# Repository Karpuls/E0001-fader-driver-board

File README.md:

# E0001 – Motorized fader driver board

Controller board for an ALPS **RSA0N11M9A0J**-compatible motorized, touch-sensitive 100 mm fader
(Amazon.de B0H45B29YK clone). The board mounts under the fader, soldered to its pins.

- **Rev B (current):** STM32C051F6P6, DRV8210P H-bridge (motor from 5 V), MCP1703A 3.3 V LDO,
  capacitive touch on the fader lever, position from the 10k linear track, 4-layer, 107 × 17 mm.
- **Interface:** JST GH 4-pin horizontal, Pixhawk/Dronecode I2C pinout (1 = +5 V, 2 = SCL, 3 = SDA, 4 = GND).
  I2C pull-ups belong on the host. Address via 3 solder jumpers (bottom side), SWD via Tag-Connect TC2030-NL pads (bottom).
- Rev A (2-layer, STM32G031) is kept in `archive/revA/`.

## Layout
| Path | Content |
|---|---|
| `E0001_fader_driver.kicad_pro/.kicad_sch/.kicad_pcb` | KiCad 10 project |
| `lib/` | Fader symbol/footprint/3D model + notes, STM32C051F6Px symbol |
| `bom/E0001_revB_digikey_bom.csv` | BOM (DigiKey LV part numbers, excl. fader and JST connector) |
| `mech/` | Board + fader assembly STEP and renders |
| `build/scripts/` | Generators: schematic, placement, pre-routes, Freerouting pipeline, refs, BOM (`run_all.sh`) |

## Open points
Verify the clone fader's hole pattern and pin orientation on a sample before ordering PCBs (see `lib/ALPS_RSA0N11M9A0J_notes.md`).
The ALPS 3D model in `lib/3dmodels` is ALPS CAD data; check ALPS terms before making this repository public.

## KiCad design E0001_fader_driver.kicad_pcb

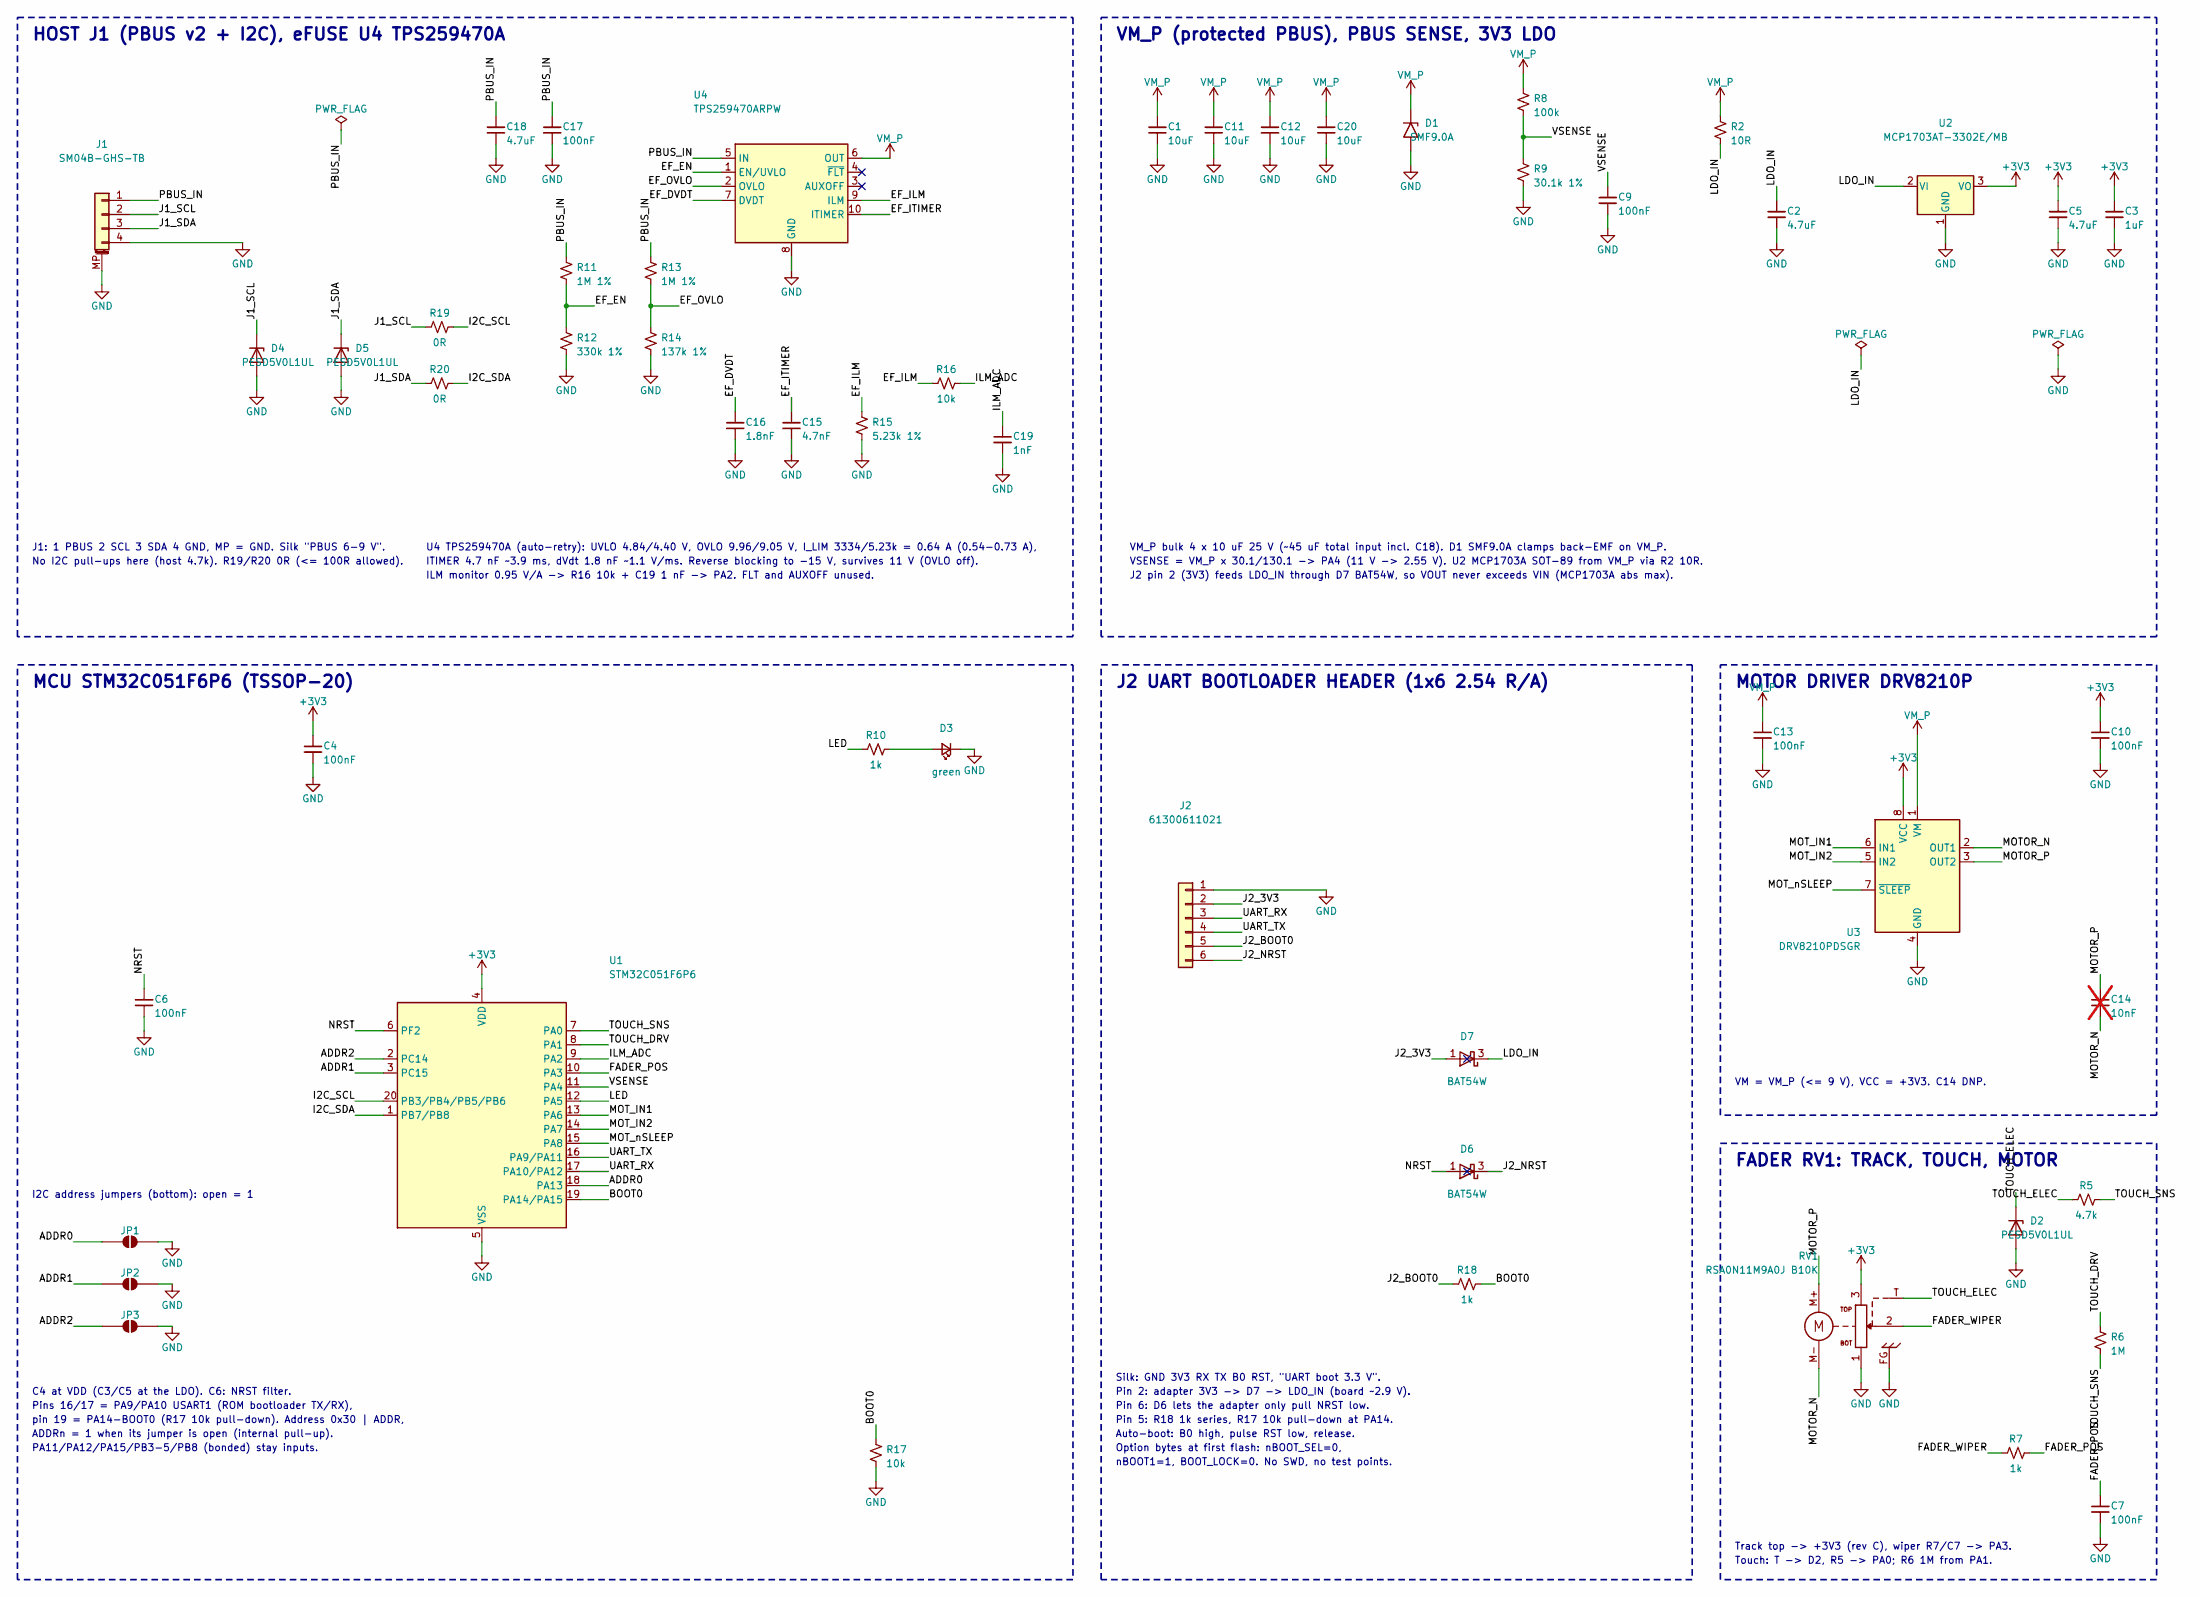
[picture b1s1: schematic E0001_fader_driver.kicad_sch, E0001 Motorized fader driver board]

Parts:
C1, C11, C12, C20: 10uF; C_0805_2012Metric; Voltage 25V; MPN TMK212BBJ106MG-T
C2, C5, C18: 4.7uF; C_0603_1608Metric; Voltage 25V; MPN GRM188R61E475KE11D
C3: 1uF; C_0402_1005Metric; MPN CL05A105KP5NNNC
C4, C6, C7, C9, C10, C13, C17: 100nF; C_0402_1005Metric; Voltage 50V; MPN GRM155R71H104KE14D
C14: 10nF; C_0402_1005Metric; Voltage 50V; MPN GRM155R71H103KA88D; not fitted
C15: 4.7nF; C_0402_1005Metric; Voltage 50V; MPN GRM155R71H472KA01J
C16: 1.8nF; C_0402_1005Metric; Voltage 50V; MPN C0402C182K5RACTU
C19: 1nF; C_0402_1005Metric; Voltage 50V; MPN GRM155R71H102KA01D
D1: SMF9.0A; D_SOD-123F; MPN SMF9.0A
D2, D4, D5: PESD5V0L1UL; D_SOD-882; MPN PESD5V0L1UL,315
D3: green; LED_0603_1608Metric; MPN LTST-C191KGKT
D6, D7: BAT54W; SOT-323_SC-70; MPN BAT54W,135
J1: SM04B-GHS-TB; JST_GH_SM04B-GHS-TB_1x04-1MP_P1.25mm_Horizontal; MPN SM04B-GHS-TB(LF)(SN)
J2: 61300611021; PinHeader_1x06_P2.54mm_Horizontal; MPN 61300611021
JP1: ADDR0; SolderJumper-2_P1.3mm_Open_RoundedPad1.0x1.5mm
JP2: ADDR1; SolderJumper-2_P1.3mm_Open_RoundedPad1.0x1.5mm
JP3: ADDR2; SolderJumper-2_P1.3mm_Open_RoundedPad1.0x1.5mm
R2: 10R; R_0603_1608Metric; MPN RC0603FR-0710RL
R5: 4.7k; R_0402_1005Metric; MPN RK73H1ETTP4701F
R6: 1M; R_0402_1005Metric; MPN RC0402FR-071ML
R7, R10, R18: 1k; R_0402_1005Metric; MPN RC0402FR-071KL
R8: 100k; R_0402_1005Metric; MPN RC0402FR-07100KL
R9: 30.1k 1%; R_0402_1005Metric; MPN RC0402FR-0730K1L
R11, R13: 1M 1%; R_0402_1005Metric; MPN RC0402FR-071ML
R12: 330k 1%; R_0402_1005Metric; MPN RC0402FR-07330KL
R14: 137k 1%; R_0402_1005Metric; MPN RC0402FR-07137KL
R15: 5.23k 1%; R_0402_1005Metric; MPN RC0402FR-075K23L
R16, R17: 10k; R_0402_1005Metric; MPN RC0402FR-0710KL
R19, R20: 0R; R_0402_1005Metric; MPN RC0402JR-070RL
RV1: RSA0N11M9A0J B10K; ALPS_RSA0N11M9A0J; MPN RSA0N11M9A0J B10K clone
U1: STM32C051F6P6; TSSOP-20_4.4x6.5mm_P0.65mm; MPN STM32C051F6P6
U2: MCP1703AT-3302E/MB; SOT-89-3; MPN MCP1703AT-3302E/MB
U3: DRV8210PDSGR; Texas_DSG0008A_WSON-8-1EP_2x2mm_P0.5mm_EP0.9x1.6mm; MPN DRV8210PDSGR
U4: TPS259470ARPW; TI_RPW0010A_VQFN-HR-10_2x2mm_P0.475mm; MPN TPS259470ARPWR

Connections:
+3V3: C3.1, C4.1, C5.1, C10.1, RV1.3 (END_TOP), U1.4 (VDD), U2.3 (VO), U3.8 (VCC)
/ADDR0: JP1.1 (A), U1.18 (PA13)
/ADDR1: JP2.1 (A), U1.3 (PC15)
/ADDR2: JP3.1 (A), U1.2 (PC14)
/BOOT0: R17.1, R18.2, U1.19 (PA14/PA15)
/EF_DVDT: C16.1, U4.7 (DVDT)
/EF_EN: R11.2, R12.1, U4.1 (EN/UVLO)
/EF_ILM: R15.1, R16.1, U4.9 (ILM)
/EF_ITIMER: C15.1, U4.10 (ITIMER)
/EF_OVLO: R13.2, R14.1, U4.2 (OVLO)
/FADER_POS: C7.1, R7.2, U1.10 (PA3)
/FADER_WIPER: R7.1, RV1.2 (WIPER)
/I2C_SCL: R19.2, U1.20 (PB3/PB4/PB5/PB6)
/I2C_SDA: R20.2, U1.1 (PB7/PB8)
/ILM_ADC: C19.1, R16.2, U1.9 (PA2)
/J1_SCL: D4.1 (K), J1.2, R19.1
/J1_SDA: D5.1 (K), J1.3, R20.1
/J2_3V3: D7.1 (A), J2.2
/J2_BOOT0: J2.5, R18.1
/J2_NRST: D6.3 (K), J2.6
/LDO_IN: C2.1, D7.3 (K), R2.2, U2.2 (VI)
/LED: R10.1, U1.12 (PA5)
/MOTOR_N: C14.2, RV1.M-, U3.2 (OUT1)
/MOTOR_P: C14.1, RV1.M+, U3.3 (OUT2)
/MOT_IN1: U1.13 (PA6), U3.6 (IN1)
/MOT_IN2: U1.14 (PA7), U3.5 (IN2)
/MOT_nSLEEP: U1.15 (PA8), U3.7 (~SLEEP)
/NRST: C6.1, D6.1 (A), U1.6 (PF2)
/PBUS_IN: C17.1, C18.1, J1.1, R11.1, R13.1, U4.5 (IN)
/TOUCH_DRV: R6.1, U1.8 (PA1)
/TOUCH_ELEC: D2.1 (K), R5.1, RV1.T (TOUCH)
/TOUCH_SNS: R5.2, R6.2, U1.7 (PA0)
/UART_RX: J2.3, U1.17 (PA10/PA12)
/UART_TX: J2.4, U1.16 (PA9/PA11)
/VSENSE: C9.1, R8.2, R9.1, U1.11 (PA4)
GND: C1.2, C2.2, C3.2, C4.2, C5.2, C6.2, C7.2, C9.2, C10.2, C11.2, C12.2, C13.2, C15.2, C16.2, C17.2, C18.2, C19.2, C20.2, D1.2 (A2), D2.2 (A), D3.1 (K), D4.2 (A), D5.2 (A), J1.4, J1.MP (MountPin), J2.1, JP1.2 (B), JP2.2 (B), JP3.2 (B), R9.2, R12.2, R14.2, R15.2, R17.2, RV1.1 (END_BOT), RV1.FG (FRAME), U1.5 (VSS), U2.1 (GND), U3.4 (GND), U3.9 (GND), U4.8 (GND)
unnamed: D3.2 (A), R10.2
VM_P: C1.1, C11.1, C12.1, C13.1, C20.1, D1.1 (A1), R2.1, R8.1, U3.1 (VM), U4.6 (OUT)

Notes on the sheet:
HOST J1 (PBUS v2 + I2C), eFUSE U4 TPS259470A
J1: 1 PBUS 2 SCL 3 SDA 4 GND, MP = GND. Silk "PBUS 6-9 V".
No I2C pull-ups here (host 4.7k). R19/R20 0R (<= 100R allowed).
U4 TPS259470A (auto-retry): UVLO 4.84/4.40 V, OVLO 9.96/9.05 V, I_LIM 3334/5.23k = 0.64 A (0.54-0.73 A),
ITIMER 4.7 nF ~3.9 ms, dVdt 1.8 nF ~1.1 V/ms. Reverse blocking to -15 V, survives 11 V (OVLO off).
ILM monitor 0.95 V/A -> R16 10k + C19 1 nF -> PA2. FLT and AUXOFF unused.
VM_P (protected PBUS), PBUS SENSE, 3V3 LDO
VM_P bulk 4 x 10 uF 25 V (~45 uF total input incl. C18). D1 SMF9.0A clamps back-EMF on VM_P.
VSENSE = VM_P x 30.1/130.1 -> PA4 (11 V -> 2.55 V). U2 MCP1703A SOT-89 from VM_P via R2 10R.
J2 pin 2 (3V3) feeds LDO_IN through D7 BAT54W, so VOUT never exceeds VIN (MCP1703A abs max).
MCU STM32C051F6P6 (TSSOP-20)
C4 at VDD (C3/C5 at the LDO). C6: NRST filter.
Pins 16/17 = PA9/PA10 USART1 (ROM bootloader TX/RX),
pin 19 = PA14-BOOT0 (R17 10k pull-down). Address 0x30 | ADDR,
ADDRn = 1 when its jumper is open (internal pull-up).
PA11/PA12/PA15/PB3-5/PB8 (bonded) stay inputs.
I2C address jumpers (bottom): open = 1
J2 UART BOOTLOADER HEADER (1x6 2.54 R/A)
Silk: GND 3V3 RX TX B0 RST, "UART boot 3.3 V".
Pin 2: adapter 3V3 -> D7 -> LDO_IN (board ~2.9 V).
Pin 6: D6 lets the adapter only pull NRST low.
Pin 5: R18 1k series, R17 10k pull-down at PA14.
Auto-boot: B0 high, pulse RST low, release.
Option bytes at first flash: nBOOT_SEL=0,
nBOOT1=1, BOOT_LOCK=0. No SWD, no test points.
MOTOR DRIVER DRV8210P
VM = VM_P (<= 9 V), VCC = +3V3. C14 DNP.
FADER RV1: TRACK, TOUCH, MOTOR
Track top -> +3V3 (rev C), wiper R7/C7 -> PA3.
Touch: T -> D2, R5 -> PA0; R6 1M from PA1.

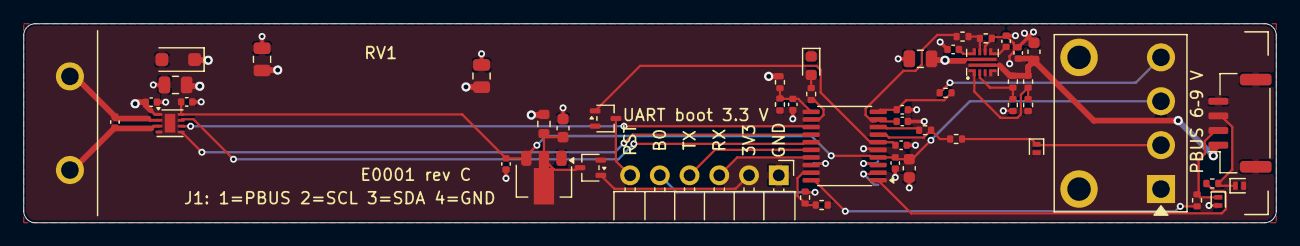
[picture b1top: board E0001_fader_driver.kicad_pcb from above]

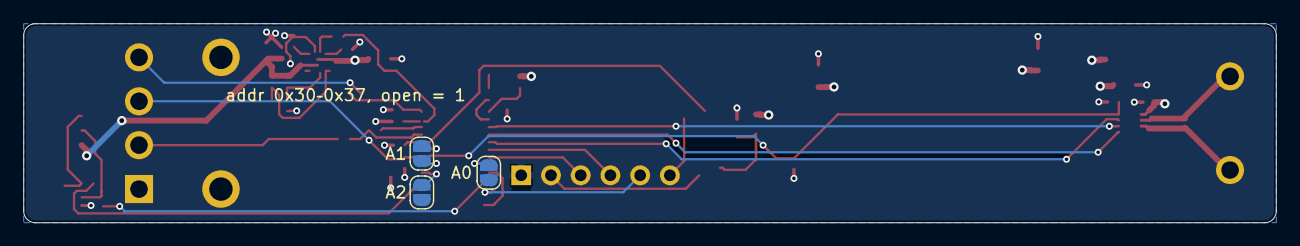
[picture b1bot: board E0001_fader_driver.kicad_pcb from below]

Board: 4 copper layers, 107.0 x 17.0 mm, 53 parts (3 on the bottom side), 38 nets.

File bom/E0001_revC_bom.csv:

Supplier,Qty,QtyBasis,References,Value,Footprint,MPN,Manufacturer,SupplierPN,Stock,Lifecycle,UnitEUR,LeadWeeks,DNP,OwnerStock,Notes
DigiKey,1,spec,U1,STM32C051F6P6,TSSOP-20,STM32C051F6P6,STMicroelectronics,497-STM32C051F6P6-ND,47,Active,1.28,52,,no,"Approved alternate STM32C051F8P6 (same TSSOP-20 pinout, 64 KB): 497-STM32C051F8P6-ND, stock 1178, EUR 1.34. Buy whichever is in stock."
DigiKey,1,spec,U2,3.3 V LDO,**SOT-89-3**,MCP1703AT-3302E/MB,Microchip Technology,MCP1703AT-3302E/MBCT-ND,9366,Active,0.66,8,,no,
DigiKey,1,spec,U3,H-bridge,WSON-8 2×2,DRV8210PDSGR,Texas Instruments,296-DRV8210PDSGRCT-ND,3849,Active,0.76,12,,no,
DigiKey,1,spec,U4,eFuse,VQFN-HR-10 2×2 (RPW),TPS259470ARPWR,Texas Instruments,296-TPS259470ARPWRCT-ND,78910,Active,1.81,12,,no,
LCSC,1,spec,J1,JST-GH 4p,SM04B-GHS-TB horizontal,SM04B-GHS-TB(LF)(SN),JST Sales America Inc.,LCSC C189895 (SM04B-GHS-TB(LF)(SN)),"1900 (LCSC, 2026-10-19)",Active,0.31 USD @5 (LCSC),16,,yes,"DigiKey 455-1566-1-ND stock 0 (16 w). Second sources: RS Online 1755704 / 7521797 (regional stock), LCSC C189895 (min order 5). E0003 uses the same LCSC part."
DigiKey,1,spec,J2,1×6 2.54 R/A,PinHeader_1x06_P2.54mm_Horizontal,61300611021,Würth Elektronik,732-5339-ND,6816,Active,0.47,18,,no,
Amazon.de,1,spec,RV1,Motor fader 10 k lin,ALPS_RSA0N11M9A0J,RSA0N11M9A0J B10K clone,Fastigeaty (seller Fadianshop),ASIN B0H45B29YK,not checked (Amazon page blocked),-,,,,yes,"ALPS RSA0N11M9A0J-compatible clone, 100 mm motor fader Owner has the faders (flag only; full quantity stays)."
DigiKey,1,spec,D1,SMF9.0A,D_SOD-123F (SMF),SMF9.0A,Littelfuse Inc.,F5755CT-ND,2437,Active,0.47,20,,no,
DigiKey,3,spec,D2 D4 D5,ESD,D_SOD-882,"PESD5V0L1UL,315",Nexperia USA Inc.,1727-4193-1-ND,18740,Active,0.22,30,,no,
DigiKey,1,spec,D3,LED green,0603,LTST-C191KGKT,Lite-On Inc.,160-1446-1-ND,2812317,Active,0.13,14,,no,
DigiKey,2,spec,D6 D7,Schottky,SOT-323,"BAT54W,135",Nexperia USA Inc.,1727-1869-1-ND,26776,Active,0.17,30,,no,
DigiKey,4,spec,C1 C11 C12 C20,10 µF 25 V X5R,0805,TMK212BBJ106MG-T,Taiyo Yuden,587-6025-1-ND,237658,Active,0.18,23,,no,
DigiKey,3,spec,C2 C5 C18,4.7 µF 25 V,0603,GRM188R61E475KE11D,Murata Electronics,490-7203-1-ND,713624,Active,0.21,17,,no,
DigiKey,1,spec,C3,1 µF 10 V,0402,CL05A105KP5NNNC,Samsung Electro-Mechanics,1276-1076-1-ND,911254,Active,0.09,61,,no,
DigiKey,7,spec,C4 C6 C7 C9 C10 C13 C17,100 nF 50 V X7R,0402,GRM155R71H104KE14D,Murata Electronics,490-10700-1-ND,1430736,Active,0.09,17,,no,
DigiKey,1,spec,C14,10 nF 50 V,0402,GRM155R71H103KA88D,Murata Electronics,490-4516-1-ND,4127456,Active,0.09,17,DNP,no,
DigiKey,1,spec,C15,4.7 nF 50 V (ITIMER),0402,GRM155R71H472KA01J,Murata Electronics,490-8259-1-ND,143253,Active,0.09,17,,no,
DigiKey,1,spec,C16,1.8 nF 50 V (dVdt),0402,C0402C182K5RACTU,KEMET,399-C0402C182K5RACTUCT-ND,9731,Active,0.44,17,,no,
DigiKey,1,spec,C19,1 nF 50 V (ILM ADC),0402,GRM155R71H102KA01D,Murata Electronics,490-1303-1-ND,4189153,Active,0.1,21,,no,
DigiKey,1,spec,R2,10 Ω,0603,RC0603FR-0710RL,YAGEO,311-10.0HRCT-ND,264276,Active,0.1,22,,no,
DigiKey,1,spec,R5,4.7 kΩ,0402,RK73H1ETTP4701F,"KOA Speer Electronics, Inc.",2019-RK73H1ETTP4701FCT-ND,2889565,Active,0.09,7,,no,
DigiKey,3,spec,R6 R11 R13,1 MΩ 1 %,0402,RC0402FR-071ML,YAGEO,311-1.00MLRCT-ND,961162,Active,0.09,22,,no,
DigiKey,3,spec,R7 R10 R18,1 kΩ,0402,RC0402FR-071KL,YAGEO,311-1.00KLRCT-ND,3584811,Active,0.09,22,,no,
DigiKey,1,spec,R8,100 kΩ,0402,RC0402FR-07100KL,YAGEO,311-100KLRCT-ND,6147223,Active,0.09,22,,no,
DigiKey,1,spec,R9,30.1 kΩ 1 %,0402,RC0402FR-0730K1L,YAGEO,311-30.1KLRCT-ND,12740,Active,0.09,22,,no,
DigiKey,1,spec,R12,330 kΩ 1 %,0402,RC0402FR-07330KL,YAGEO,311-330KLRCT-ND,902151,Active,0.09,22,,no,
DigiKey,1,spec,R14,137 kΩ 1 %,0402,RC0402FR-07137KL,YAGEO,YAG2972CT-ND,126860,Active,0.09,22,,no,
DigiKey,1,spec,R15,5.23 kΩ 1 %,0402,RC0402FR-075K23L,YAGEO,YAG3195CT-ND,39950,Active,0.09,22,,no,
DigiKey,2,spec,R16 R17,10 kΩ,0402,RC0402FR-0710KL,YAGEO,311-10.0KLRCT-ND,10874291,Active,0.09,22,,no,
DigiKey,2,spec,R19 R20,0 Ω,0402,RC0402JR-070RL,YAGEO,311-0.0JRCT-ND,1032165,Active,0.09,22,,no,
PCB,3,spec,JP1 JP2 JP3,solder jumper,SolderJumper-2 open,—,-,-,-,-,0,,,no,"Open solder jumper (PCB feature, no part)"

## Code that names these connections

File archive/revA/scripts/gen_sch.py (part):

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R('R8', '100k', 101.6, ry_ + 5.08)
wire((101.6, ry_), pin('R8', '1'))
R('R9', '100k', 101.6, ry_ + 15.24)
wire(pin('R8', '2'), pin('R9', '1'), net='VSENSE')
gnd_under('R9')
nd = (101.6, ry_ + 10.16)
junction(nd)
place('Device:C_Small', 'C9', '100nF', 93.98, nd[1] + 5.08, 0, fp=C_FP,
      refpos=(92.202, nd[1] + 4.445, 0, 'right'), valpos=(92.202, nd[1] + 6.985, 0, 'right'))
wire(nd, (93.98, nd[1]), (88.9, nd[1]), net='VSENSE')
wire((93.98, nd[1]), pin('C9', '1'), net='VSENSE'); junction((93.98, nd[1]))
gnd_under('C9')
label('VSENSE', (88.9, nd[1]), 'left')
text('VSENSE = +5 V / 2  (PA4)', 86.36, 67.31, 1.27, color=C_PWR)

# =========================================================================
# B. 3.3 V LDO
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      refpos=(157.48, yl - 10.16, 0, None), valpos=(157.48, yl - 7.62, 0, None),
      extra={'MPN': 'MCP1703AT-3302E/CB', 'Manufacturer': 'Microchip'})
vi, vo, ug = pin('U2', '3'), pin('U2', '2'), pin('U2', '1')
wire(pin('R2', '2'), vi, net='LDO_IN')
label('LDO_IN', (130.81, yl), 'right')
C('C2', '4.7uF', 140.97, yl + 5.08, fp='Capacitor_SMD:C_0603_1608Metric', extra={'Voltage': '10V', 'Dielectric': 'X5R'})
wire((140.97, yl), pin('C2', '1')); junction((140.97, yl))
gnd_under('C2')
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        junction((xc, top))
    gnd_under(ref)
o1, o2 = pin('U3', '2'), pin('U3', '3')
wire(o1, (256.54, o1[1]), net='MOTOR_N'); label('MOTOR_N', (256.54, o1[1]), 'right')
wire(o2, (256.54, o2[1]), net='MOTOR_P'); label('MOTOR_P', (256.54, o2[1]), 'right')
C('C14', '10nF', 248.92, o2[1] + 5.08, dnp=True)
wire((248.92, o2[1]), pin('C14', '1'), net='MOTOR_P'); junction((248.92, o2[1]))
wire(pin('C14', '2'), (248.92, 53.34), (256.54, 53.34), net='MOTOR_N')
label('MOTOR_N', (256.54, 53.34), 'right')
text('C13 = VCC, C10-C12 = VM decoupling. C14 not fitted (brush-noise option).', 185.42, 67.31, 1.27)
text('IN2 = PWM, IN1 = 0: M+ positive, knob moves to the top of travel (ALPS).', 185.42, 70.485, 1.27)
text('IN1 = PWM, IN2 = 0: knob moves down.  IN1 = IN2 = 1: brake.', 185.42, 73.66, 1.27)
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pt, pb, pw, ptc, pfg = pin('RV1', '3'), pin('RV1', '1'), pin('RV1', '2'), pin('RV1', 'T'), pin('RV1', 'FG')
pmp, pmn = pin('RV1', 'M+'), pin('RV1', 'M-')
wire(pt, (pt[0], 106.68), net='POT_HI'); label('POT_HI', (pt[0], 106.68), 'up')
wire(pmp, (pmp[0], 109.22), (190.5, 109.22), net='MOTOR_P'); label('MOTOR_P', (190.5, 109.22), 'left')
wire(pmn, (pmn[0], 134.62), (190.5, 134.62), net='MOTOR_N'); label('MOTOR_N', (190.5, 134.62), 'left')
wire(pb, (pb[0], 133.35)); power('gnd', (pb[0], 133.35))
wire(pfg, (pfg[0], 133.35)); power('gnd', (pfg[0], 133.35))
# touch network
yt = 106.68
wire(ptc, (215.9, ptc[1]), (215.9, yt), (238.76, yt), net='TOUCH_ELEC')
label('TOUCH_ELEC', (216.535, yt), 'right')
place('Diode:PESD5V0L1UL', 'D2', 'PESD5V0L1UL', 231.14, yt + 3.81, 270,
      refpos=(233.68, yt + 3.175, 0, 'left'), valpos=(233.68, yt + 5.715, 0, 'left'),
      desc='Low-capacitance ESD diode on the touch line (knob is user-accessible)')
junction((231.14, yt))
power('gnd', pin('D2', '2'))
R('R5', '4.7k', 241.3, yt, horiz=True)
wire(pin('R5', '2'), (256.54, yt), net='TOUCH_SNS')
label('TOUCH_SNS', (256.54, yt), 'right')
R('R6', '1M', 248.92, 101.6)
wire(pin('R6', '2'), (248.92, yt), net='TOUCH_SNS'); junction((248.92, yt))
wire(pin('R6', '1'), (248.92, 96.52), (254.0, 96.52), net='TOUCH_DRV')
label('TOUCH_DRV', (254.0, 96.52), 'right')
# wiper filter
R('R7', '1k', 238.76, pw[1], horiz=True)
wire(pw, pin('R7', '1'), net='FADER_WIPER')
label('FADER_WIPER', (214.63, pw[1]), 'right')
wire(pin('R7', '2'), (251.46, pw[1]), net='FADER_POS')
C('C7', '100nF', 246.38, pw[1] + 5.08)
wire((246.38, pw[1]), pin('C7', '1'), net='FADER_POS'); junction((246.38, pw[1]))
gnd_under('C7')
label('FADER_POS', (251.46, pw[1]), 'right')
text('Touch: conductive knob -> lever -> T. Sense by RC charge time (PA1 drives via 1M,', 172.72, 143.51, 1.27, color=C_TOUCH)
text('TIM2 capture on PA0) or by ADC charge sharing on PA0.', 172.72, 146.05, 1.27, color=C_TOUCH)
text('Position: track powered from POT_HI (PA2 high), wiper read on PA3 (ratiometric).', 172.72, 150.495, 1.27, color=C_ANA)
text('End 1 (bottom of travel) = GND, so FADER_POS rises toward the top.', 172.72, 153.035, 1.27, color=C_ANA)
text('FG = fader frame lugs: soldered for retention, tied to GND.', 172.72, 157.48, 1.27, color=C_ANA)

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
